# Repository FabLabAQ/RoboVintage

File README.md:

# RoboVintage
A vintage-looking robotic arm upgraded with Arduino to work with ROS

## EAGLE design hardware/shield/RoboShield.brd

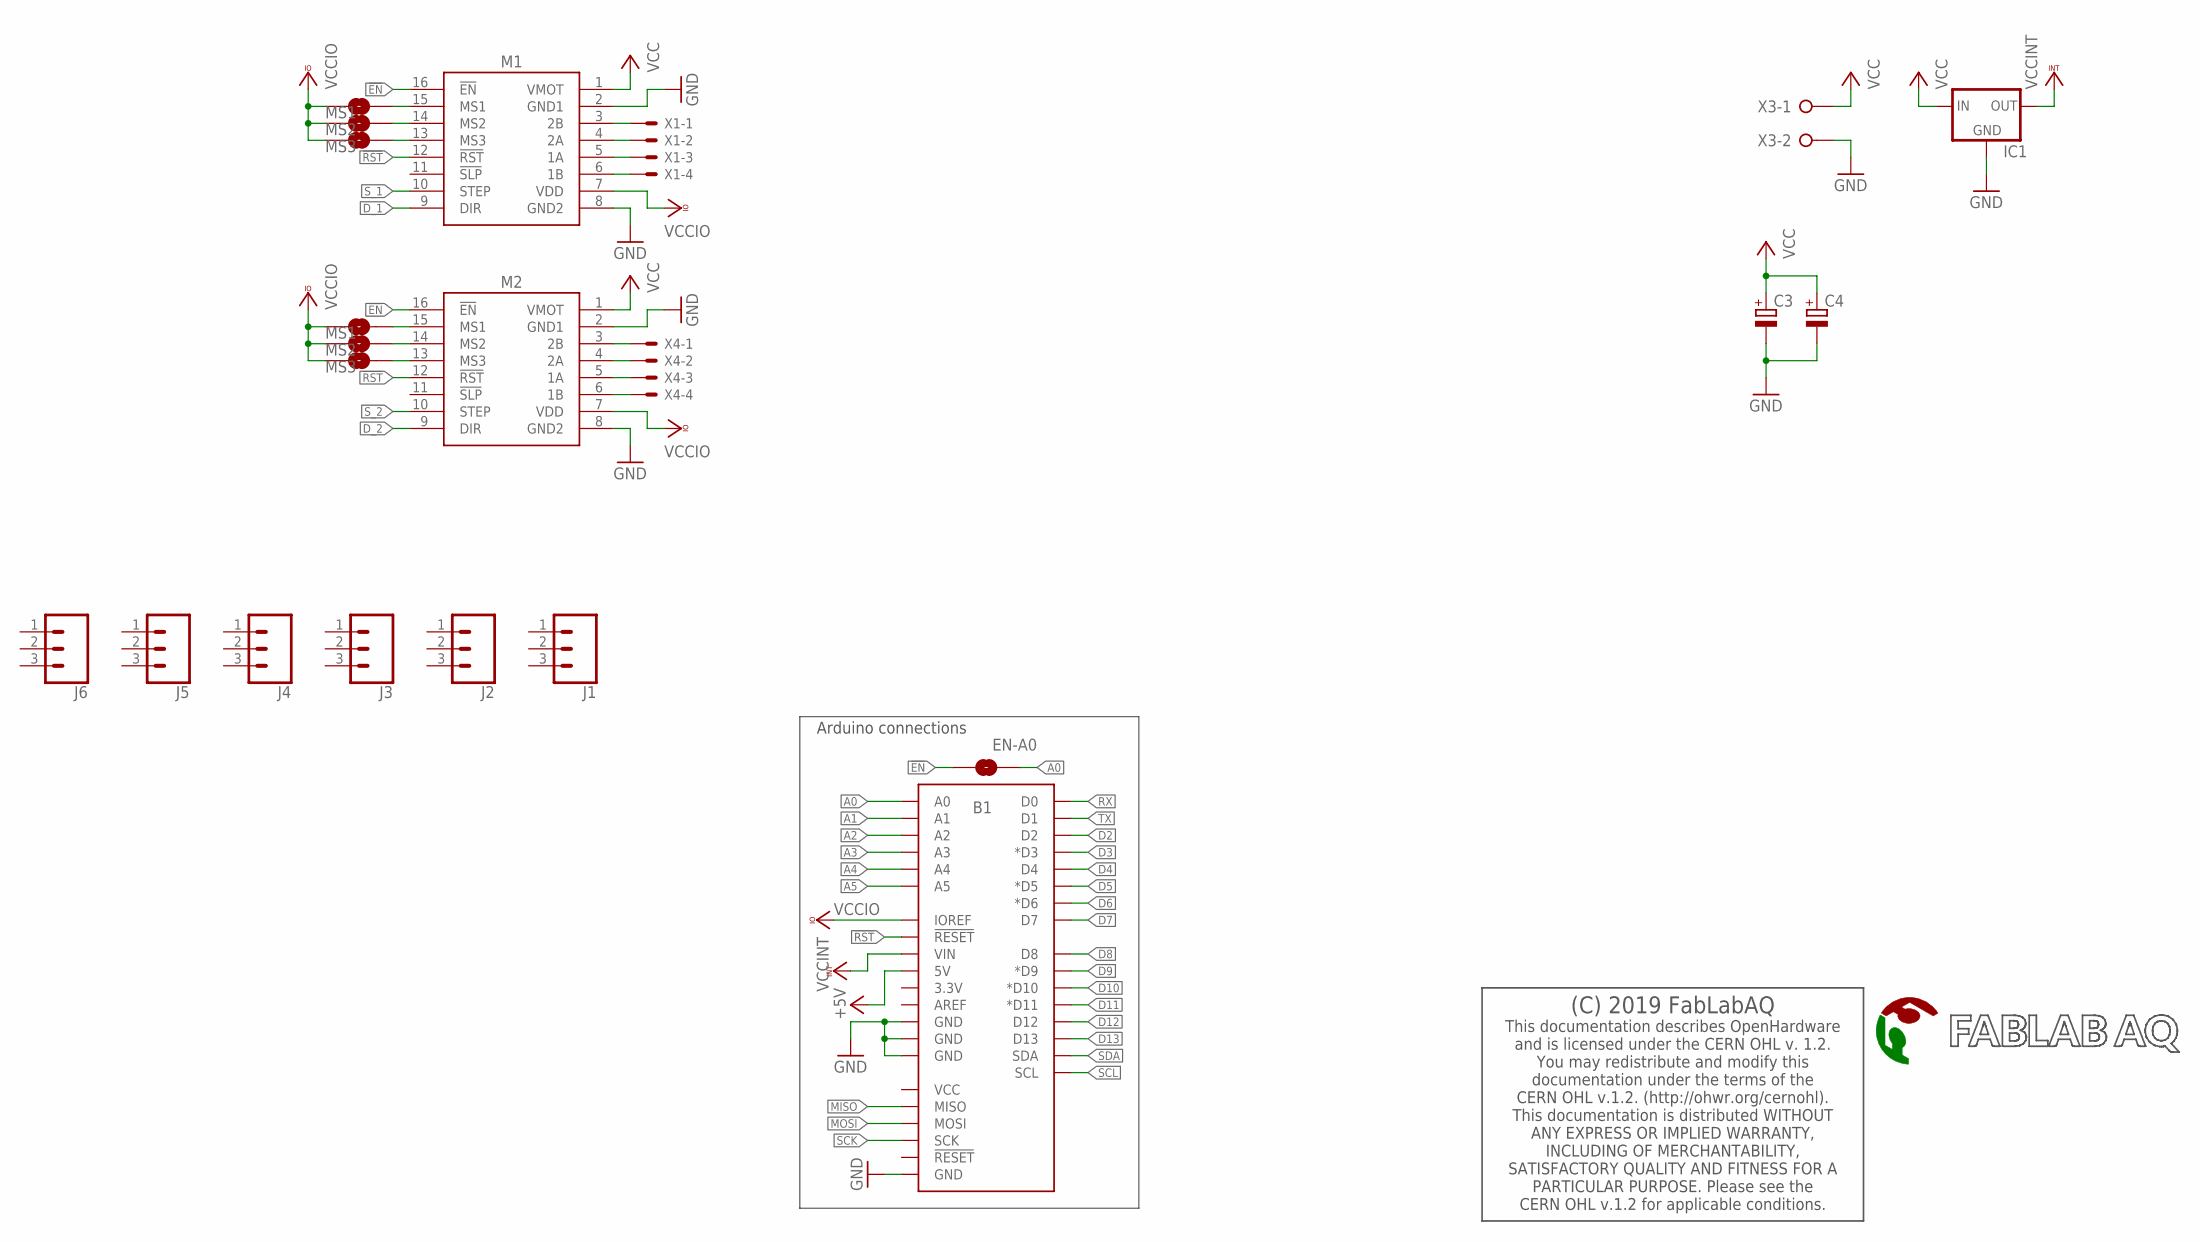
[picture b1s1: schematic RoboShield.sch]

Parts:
B1: ARDUINO_UNO_R3NO_HOLES; ARDUINO_R3_NO_HOLES
C3: CPOL-EUUD-8X10; UD-8X10_NICHICON
C4: CPOL-EUE3.5-8; E3,5-8
IC1: 78XXS
J1, J2, J3, J4, J5, J6: CONN_03; 1X03
JP1, JP5: MS1; SMT-JUMPER_2_NO_SILK
JP2, JP6: MS2; SMT-JUMPER_2_NO_SILK
JP3, JP7: MS3; SMT-JUMPER_2_NO_SILK
JP4: EN-A0; SMT-JUMPER_2_NO_SILK
M1, M2: POLOLUESTEPPERDRIVER; DIL16
U$2: (C) 2019 FabLabAQ; DOC_CERN_OHL_1.2
U$3: FABLABAQ_LOGOCENTER_20X40; SILK_CENTER_20X40
X1, X4: JST-XH-04-PIN-LONG-PAD; JST-XH-04-PACKAGE-LONG-PAD
X3: W237-02P; W237-132

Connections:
!EN: JP4.1, M1.16 (!EN), M2.16 (!EN)
!RST: B1.RESET@1 (!RESET!), M1.12 (!RST), M2.12 (!RST)
+5V: B1.5V
A0: B1.A0, JP4.2
A1: B1.A1
A2: B1.A2
A3: B1.A3
A4: B1.A4
A5: B1.A5
D2: B1.D2
D3: B1.D3 (*D3)
D4: B1.D4
D5: B1.D5 (*D5)
D6: B1.D6 (*D6)
D7: B1.D7
D8: B1.D8
D9: B1.D9 (*D9)
D10: B1.D10 (*D10)
D11: B1.D11 (*D11)
D12: B1.D12
D13: B1.D13
D_1: M1.9 (DIR)
D_2: M2.9 (DIR)
GND: B1.GND@1 (GND), B1.GND@2 (GND), B1.GND@3 (GND), B1.GND@4 (GND), C3.-, C4.-, IC1.GND, M1.2 (GND1), M1.8 (GND2), M2.2 (GND1), M2.8 (GND2), X3.2
MISO: B1.MISO
MOSI: B1.MOSI
unnamed: M1.3 (2B), X1.1
unnamed: M1.4 (2A), X1.2
unnamed: M1.5 (1A), X1.3
unnamed: M1.6 (1B), X1.4
unnamed: M2.3 (2B), X4.1
unnamed: M2.4 (2A), X4.2
unnamed: M2.5 (1A), X4.3
unnamed: JP2.2, M1.14 (MS2)
unnamed: JP3.2, M1.13 (MS3)
unnamed: JP1.2, M1.15 (MS1)
unnamed: M2.6 (1B), X4.4
unnamed: JP6.2, M2.14 (MS2)
unnamed: JP7.2, M2.13 (MS3)
unnamed: JP5.2, M2.15 (MS1)
RX: B1.D0
SCK: B1.SCK
SCL: B1.SCL
SDA: B1.SDA
S_1: M1.10 (STEP)
S_2: M2.10 (STEP)
TX: B1.D1
VCC: C3.+, C4.+, IC1.IN, M1.1 (VMOT), M2.1 (VMOT), X3.1
VCCINT: B1.VIN, IC1.OUT
VCCIO: B1.IOREF, JP1.1, JP2.1, JP3.1, JP5.1, JP6.1, JP7.1, M1.7 (VDD), M2.7 (VDD)

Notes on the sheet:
Arduino connections

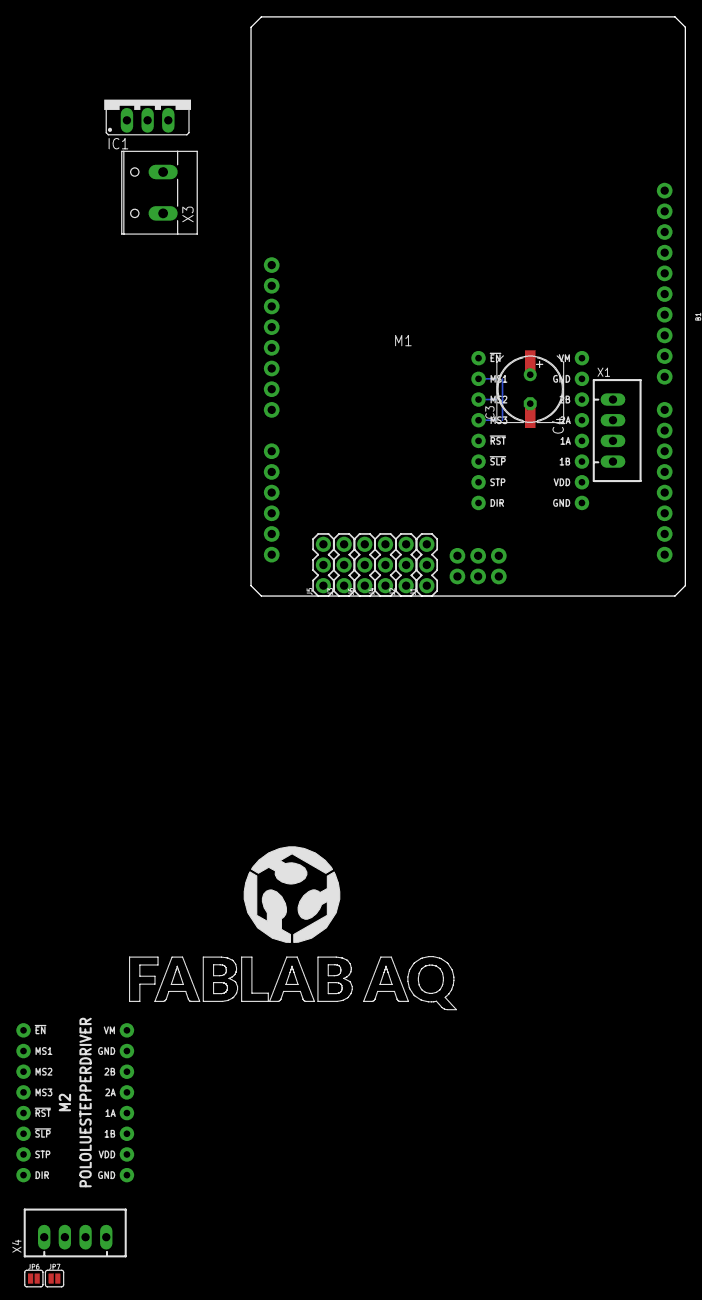
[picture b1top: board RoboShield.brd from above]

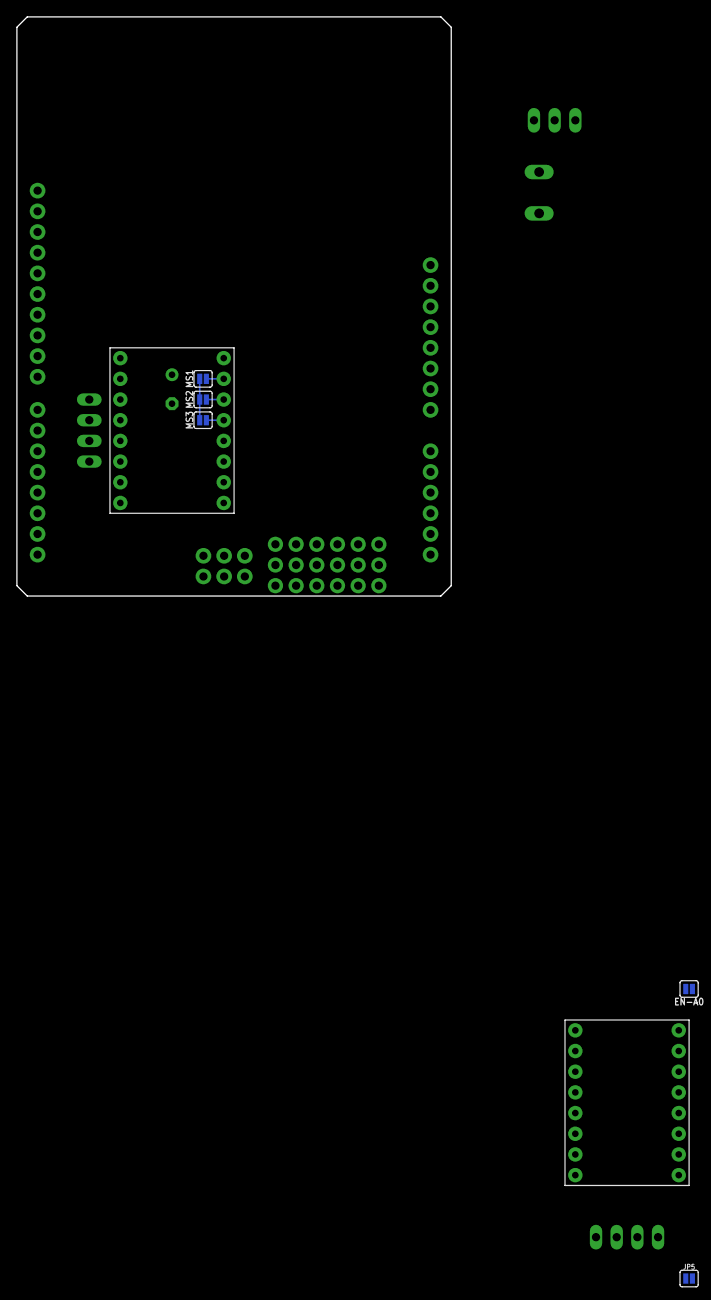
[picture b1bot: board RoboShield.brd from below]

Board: 2 copper layers, 53.3 x 71.1 mm, 24 parts (5 on the bottom side), 21 nets.

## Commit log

2019-04-07 Started shield design
2019-04-07 Added first sketch and urdf
2019-04-08 SerialStepper update

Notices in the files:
parts and their libraries:
SparkFun-Boards: Licensing: Creative Commons ShareAlike 4.0 International - https://creativecommons.org/licenses/by-sa/4.0
CERN_OHL_1.2: and is licensed under the CERN OHL v. 1.2.
documentation under the terms of the
CERN OHL v.1.2. (http://ohwr.org/cernohl).
